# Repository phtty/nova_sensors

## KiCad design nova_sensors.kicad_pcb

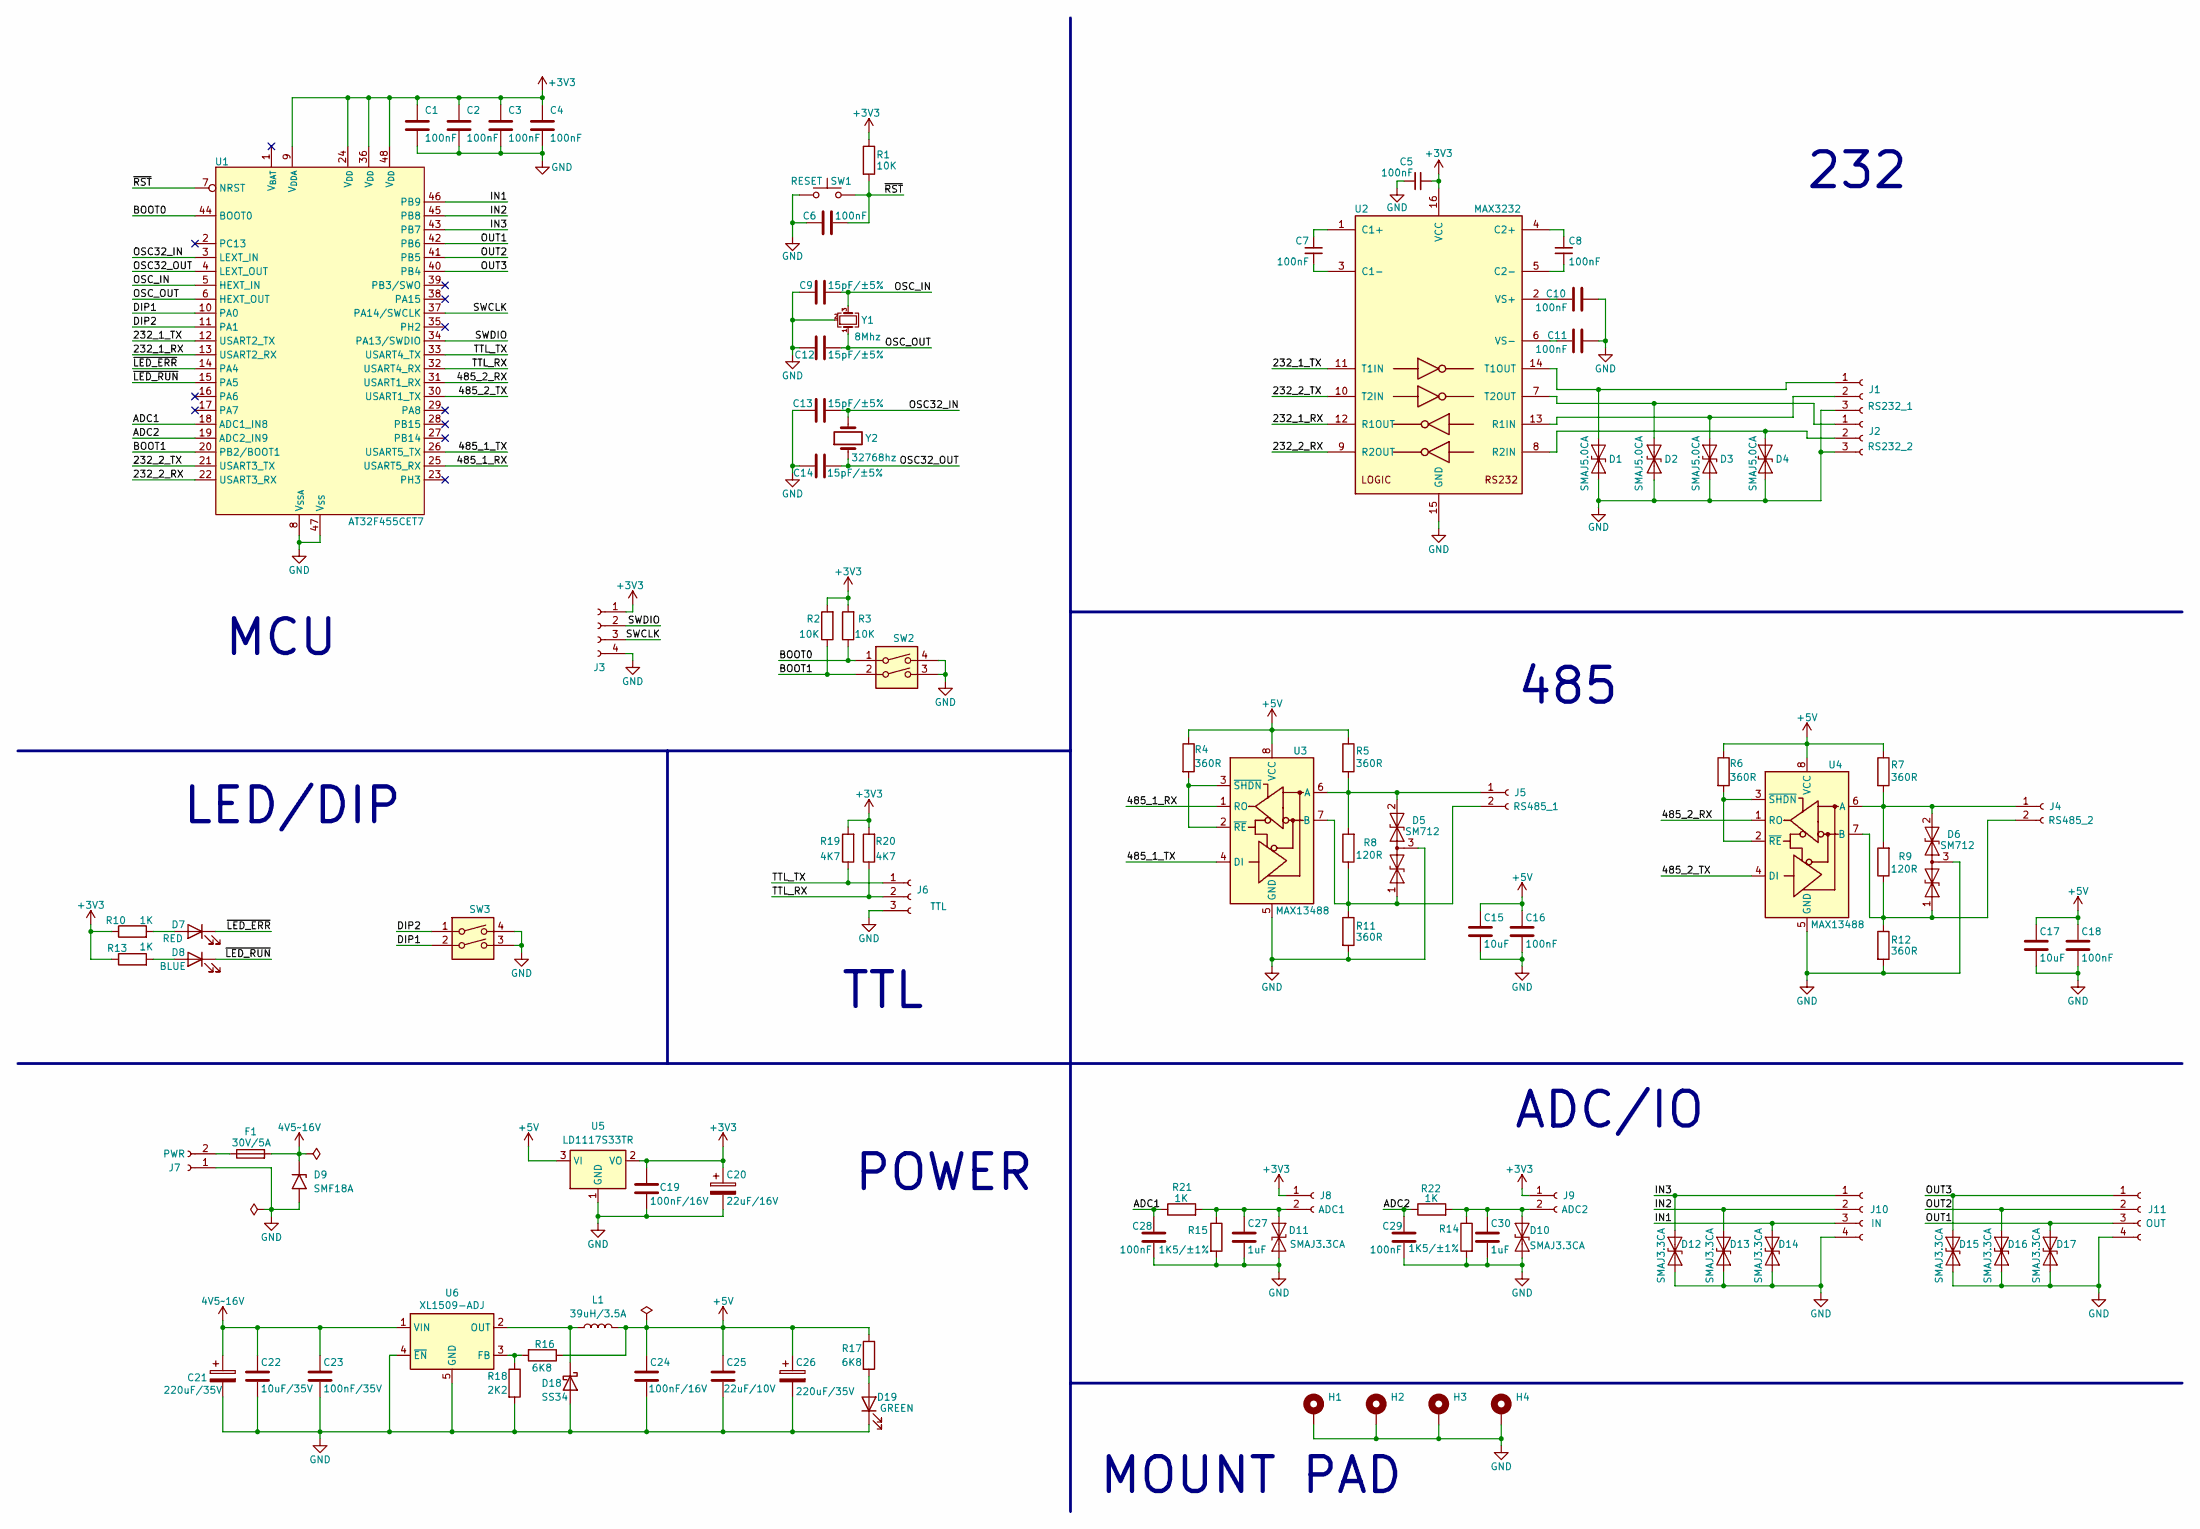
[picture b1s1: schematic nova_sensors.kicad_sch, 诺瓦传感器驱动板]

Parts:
C1, C2, C3, C4, C5, C6, C7, C8, C10, C11, C16, C18, C28, C29: 100nF; C_0603_1608Metric
C9, C12, C13, C14: 15pF/±5%; C_0603_1608Metric
C15, C17: 10uF; C_0603_1608Metric
C19, C24: 100nF/16V; C_0603_1608Metric
C20: 22uF/16V; CP_Elec_4x5.7
C21, C26: 220uF/35V; CP_Elec_8x10
C22: 10uF/35V; C_0603_1608Metric
C23: 100nF/35V; C_0603_1608Metric
C25: 22uF/10V; C_0603_1608Metric
C27, C30: 1uF; C_0603_1608Metric
D1, D2, D3, D4: SMAJ5.0CA; D_SMA
D5, D6: SM712; SOT-23
D7: RED; LED_0603_1608Metric_Pad1.05x0.95mm_HandSolder
D8: BLUE; LED_0603_1608Metric_Pad1.05x0.95mm_HandSolder
D9: SMF18A; D_SMF
D10, D11, D12, D13, D14, D15, D16, D17: SMAJ3.3CA; D_SMA
D18: SS34; D_SMA
D19: GREEN; LED_0603_1608Metric_Pad1.05x0.95mm_HandSolder
F1: 30V/5A; Fuse_1812_4532Metric_Pad1.30x3.40mm_HandSolder
H1: MountingHole_Pad; MountingHole_3.2mm_M3_Pad
H2, H3, H4: MountingHole_Pad; MountingHole_3.5mm_Pad
J1, J2, J6: Conn_01x03_Socket; PhoenixContact_MSTBA_2,5_3-G-5,08_1x03_P5.08mm_Horizontal
J3: Conn_01x04_Socket; JST_XH_B4B-XH-A_1x04_P2.50mm_Vertical
J4, J5, J7, J8, J9: Conn_01x02_Socket; PhoenixContact_MSTBA_2,5_2-G-5,08_1x02_P5.08mm_Horizontal
J10, J11: Conn_01x04_Socket; PhoenixContact_MSTBA_2,5_4-G-5,08_1x04_P5.08mm_Horizontal
L1: 39uH/3.5A; L_12x12mm_H8mm
R1, R2, R3: 10K; R_0603_1608Metric
R4, R5, R6, R7, R11, R12: 360R; R_0603_1608Metric
R8, R9: 120R; R_0603_1608Metric
R10, R13, R21, R22: 1K; R_0603_1608Metric
R14, R15: 1K5/±1%; R_0603_1608Metric
R16, R17: 6K8; R_0603_1608Metric
R18: 2K2; R_0603_1608Metric
R19, R20: 4K7; R_0603_1608Metric
SW1: SW_Push; SW_SPST_PTS647_Sx50
SW2, SW3: SW_DIP_x02; SW-SMD_2P-L5.1-W6.2-P2.54-LS9.4-BL
U1: AT32F455CET7; LQFP-48_7x7mm_P0.5mm
U2: MAX3232; SOIC-16_3.9x9.9mm_P1.27mm
U3, U4: MAX13488; SOIC-8_3.9x4.9mm_P1.27mm
U5: LD1117S33TR; SOT-223-3_TabPin2
U6: XL1509-ADJ; SOIC-8_3.9x4.9mm_P1.27mm
Y1: 8Mhz; Crystal_SMD_3225-4Pin_3.2x2.5mm
Y2: 32768hz; Crystal_SMD_3215-2Pin_3.2x1.5mm

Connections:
4V5~16V: C21.1, C22.1, C23.1, D9.1 (A1), F1.2, U6.1 (VIN)
+3V3: C1.1, C2.1, C3.1, C4.1, C5.2, C19.1, C20.1, J3.1, J8.1, J9.1, R1.1, R2.2, R3.2, R10.1, R13.1, R19.2, R20.2, U1.9 (V_{DDA}), U1.24 (V_{DD}), U1.36 (V_{DD}), U1.48 (V_{DD}), U2.16 (VCC), U5.2 (VO)
+5V: C15.1, C16.1, C17.1, C18.1, C24.1, C25.1, C26.1, L1.2, R4.1, R5.1, R6.1, R7.1, R16.1, R17.1, U3.8 (VCC), U4.8 (VCC), U5.3 (VI)
/232_1_RX: U1.13 (USART2_RX), U2.12 (R1OUT)
/232_1_TX: U1.12 (USART2_TX), U2.11 (T1IN)
/232_2_RX: U1.22 (USART3_RX), U2.9 (R2OUT)
/232_2_TX: U1.21 (USART3_TX), U2.10 (T2IN)
/485_1_RX: U1.25 (USART5_RX), U3.1 (RO)
/485_1_TX: U1.26 (USART5_TX), U3.4 (DI)
/485_2_RX: U1.31 (USART1_RX), U4.1 (RO)
/485_2_TX: U1.30 (USART1_TX), U4.4 (DI)
/ADC1: C28.1, R21.1, U1.18 (ADC1_IN8)
/ADC2: C29.1, R22.1, U1.19 (ADC2_IN9)
/BOOT0: R3.1, SW2.1, U1.44 (BOOT0)
/BOOT1: R2.1, SW2.2, U1.20 (PB2/BOOT1)
/DIP1: SW3.2, U1.10 (PA0)
/DIP2: SW3.1, U1.11 (PA1)
/IN1: D14.2 (A2), J10.3, U1.46 (PB9)
/IN2: D13.2 (A2), J10.2, U1.45 (PB8)
/IN3: D12.2 (A2), J10.1, U1.43 (PB7)
/OSC32_IN: C13.2, U1.3 (LEXT_IN), Y2.2
/OSC32_OUT: C14.1, U1.4 (LEXT_OUT), Y2.1
/OSC_IN: C9.2, U1.5 (HEXT_IN), Y1.3
/OSC_OUT: C12.1, U1.6 (HEXT_OUT), Y1.1
/OUT1: D17.2 (A2), J11.3, U1.42 (PB6)
/OUT2: D16.2 (A2), J11.2, U1.41 (PB5)
/OUT3: D15.2 (A2), J11.1, U1.40 (PB4)
/SWCLK: J3.3, U1.37 (PA14/SWCLK)
/SWDIO: J3.2, U1.34 (PA13/SWDIO)
/TTL_RX: J6.2, R20.1, U1.32 (USART4_RX)
/TTL_TX: J6.1, R19.1, U1.33 (USART4_TX)
/~LED_ERR: D7.1 (K), U1.14 (PA4)
/~LED_RUN: D8.1 (K), U1.15 (PA5)
/~RST: C6.2, R1.2, SW1.2, U1.7 (NRST)
GND: C1.2, C2.2, C3.2, C4.2, C5.1, C6.1, C9.1, C10.2, C11.2, C12.2, C13.1, C14.2, C15.2, C16.2, C17.2, C18.2, C19.2, C20.2, C21.2, C22.2, C23.2, C24.2, C25.2, C26.2, C27.2, C28.2, C29.2, C30.2, D1.1 (A1), D2.1 (A1), D3.1 (A1), D4.1 (A1), D5.3 (common), D6.3 (common), D9.2 (A2), D10.1 (A1), D11.1 (A1), D12.1 (A1), D13.1 (A1), D14.1 (A1), D15.1 (A1), D16.1 (A1), D17.1 (A1), D18.2 (A), D19.1 (K), H1.1 (1_1), H2.1 (1_1), H3.1 (1_1), H4.1 (1_1), J1.3, J2.3, J3.4, J6.3, J7.1, J10.4, J11.4, R11.2, R12.2, R14.2, R15.2, R18.2, SW1.1, SW2.3, SW2.4, SW3.3, SW3.4, U1.8 (V_{SSA}), U1.47 (V_{SS}), U2.15 (GND), U3.5 (GND), U4.5 (GND), U5.1 (GND), U6.4 (~EN), U6.5 (GND), U6.6 (GND), U6.7 (GND), U6.8 (GND), Y1.2 (G), Y1.4 (G)
unnamed: D1.2 (A2), J1.1, U2.14 (T1OUT)
unnamed: D2.2 (A2), J2.1, U2.7 (T2OUT)
unnamed: D3.2 (A2), J1.2, U2.13 (R1IN)
unnamed: D4.2 (A2), J2.2, U2.8 (R2IN)
unnamed: D5.1 (A1), J5.2, R8.1, R11.1, U3.7 (B)
unnamed: D5.2 (A2), J5.1, R5.2, R8.2, U3.6 (A)
unnamed: D6.1 (A1), J4.2, R9.1, R12.1, U4.7 (B)
unnamed: D6.2 (A2), J4.1, R7.2, R9.2, U4.6 (A)
unnamed: D7.2 (A), R10.2
unnamed: D8.2 (A), R13.2
unnamed: C30.1, D10.2 (A2), J9.2, R14.1, R22.2
unnamed: C27.1, D11.2 (A2), J8.2, R15.1, R21.2
unnamed: D18.1 (K), L1.1, U6.2 (OUT)
unnamed: D19.2 (A), R17.2
unnamed: F1.1, J7.2
unnamed: C7.1, U2.1 (C1+)
unnamed: C7.2, U2.3 (C1-)
unnamed: C8.1, U2.4 (C2+)
unnamed: C8.2, U2.5 (C2-)
unnamed: C10.1, U2.2 (VS+)
unnamed: C11.1, U2.6 (VS-)
unnamed: R4.2, U3.2 (~RE), U3.3 (~SHDN)
unnamed: R6.2, U4.2 (~RE), U4.3 (~SHDN)
unnamed: R16.2, R18.1, U6.3 (FB)

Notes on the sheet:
MOUNT PAD
LED/DIP
POWER
MCU
232
ADC/IO
485
TTL

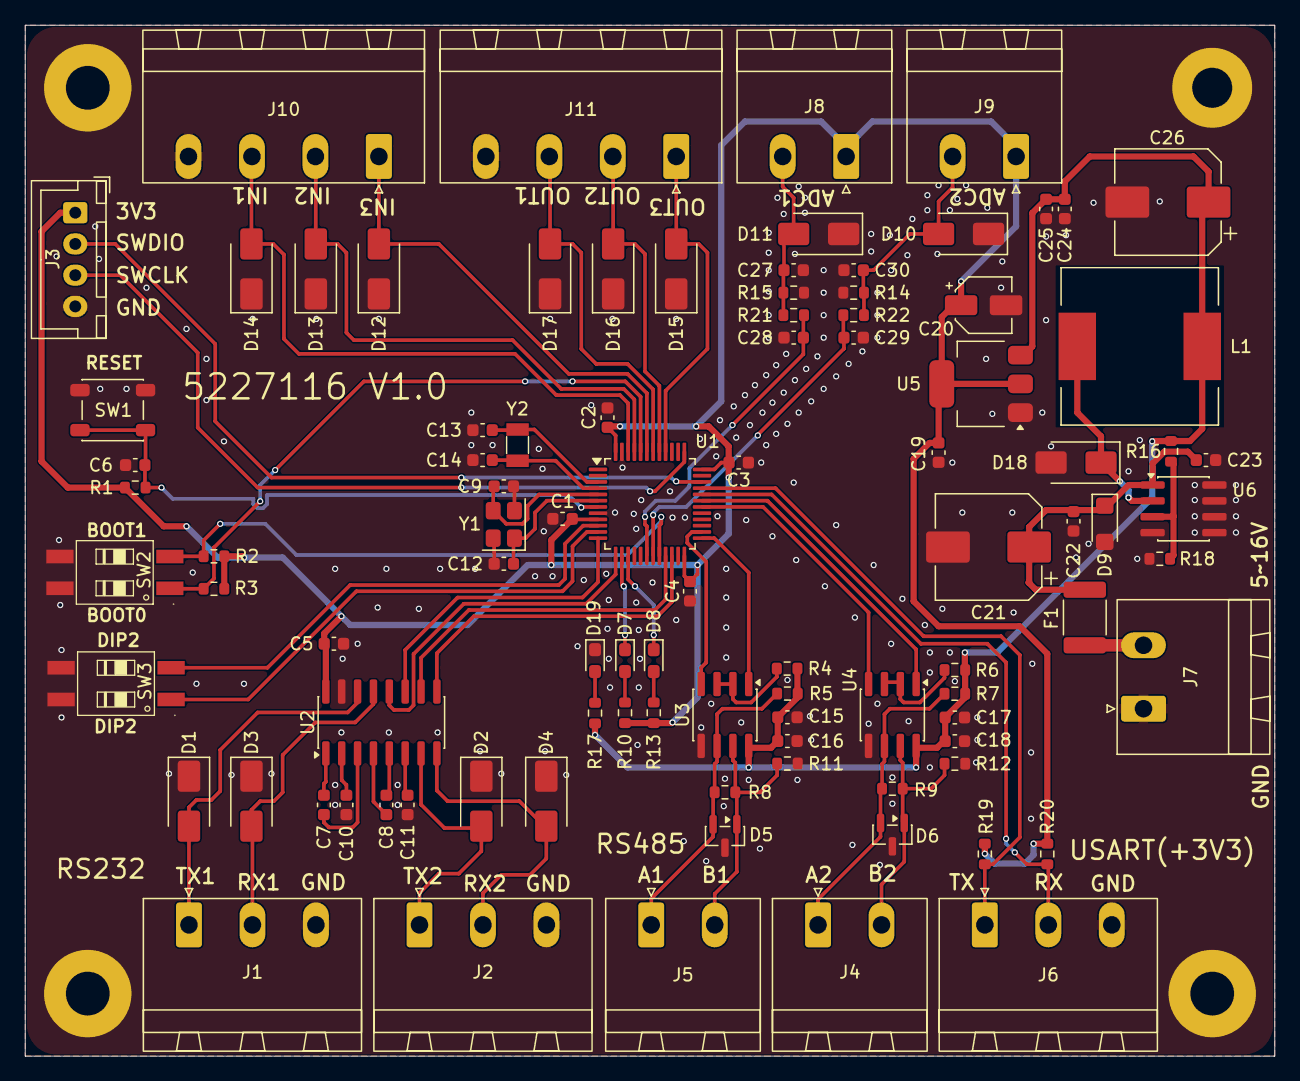
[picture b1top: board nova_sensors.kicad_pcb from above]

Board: 2 copper layers, 100.0 x 82.5 mm, 99 parts (0 on the bottom side), 59 nets.
